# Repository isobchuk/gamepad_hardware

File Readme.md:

# Schematic and PCB fo simple custom retro gamepad

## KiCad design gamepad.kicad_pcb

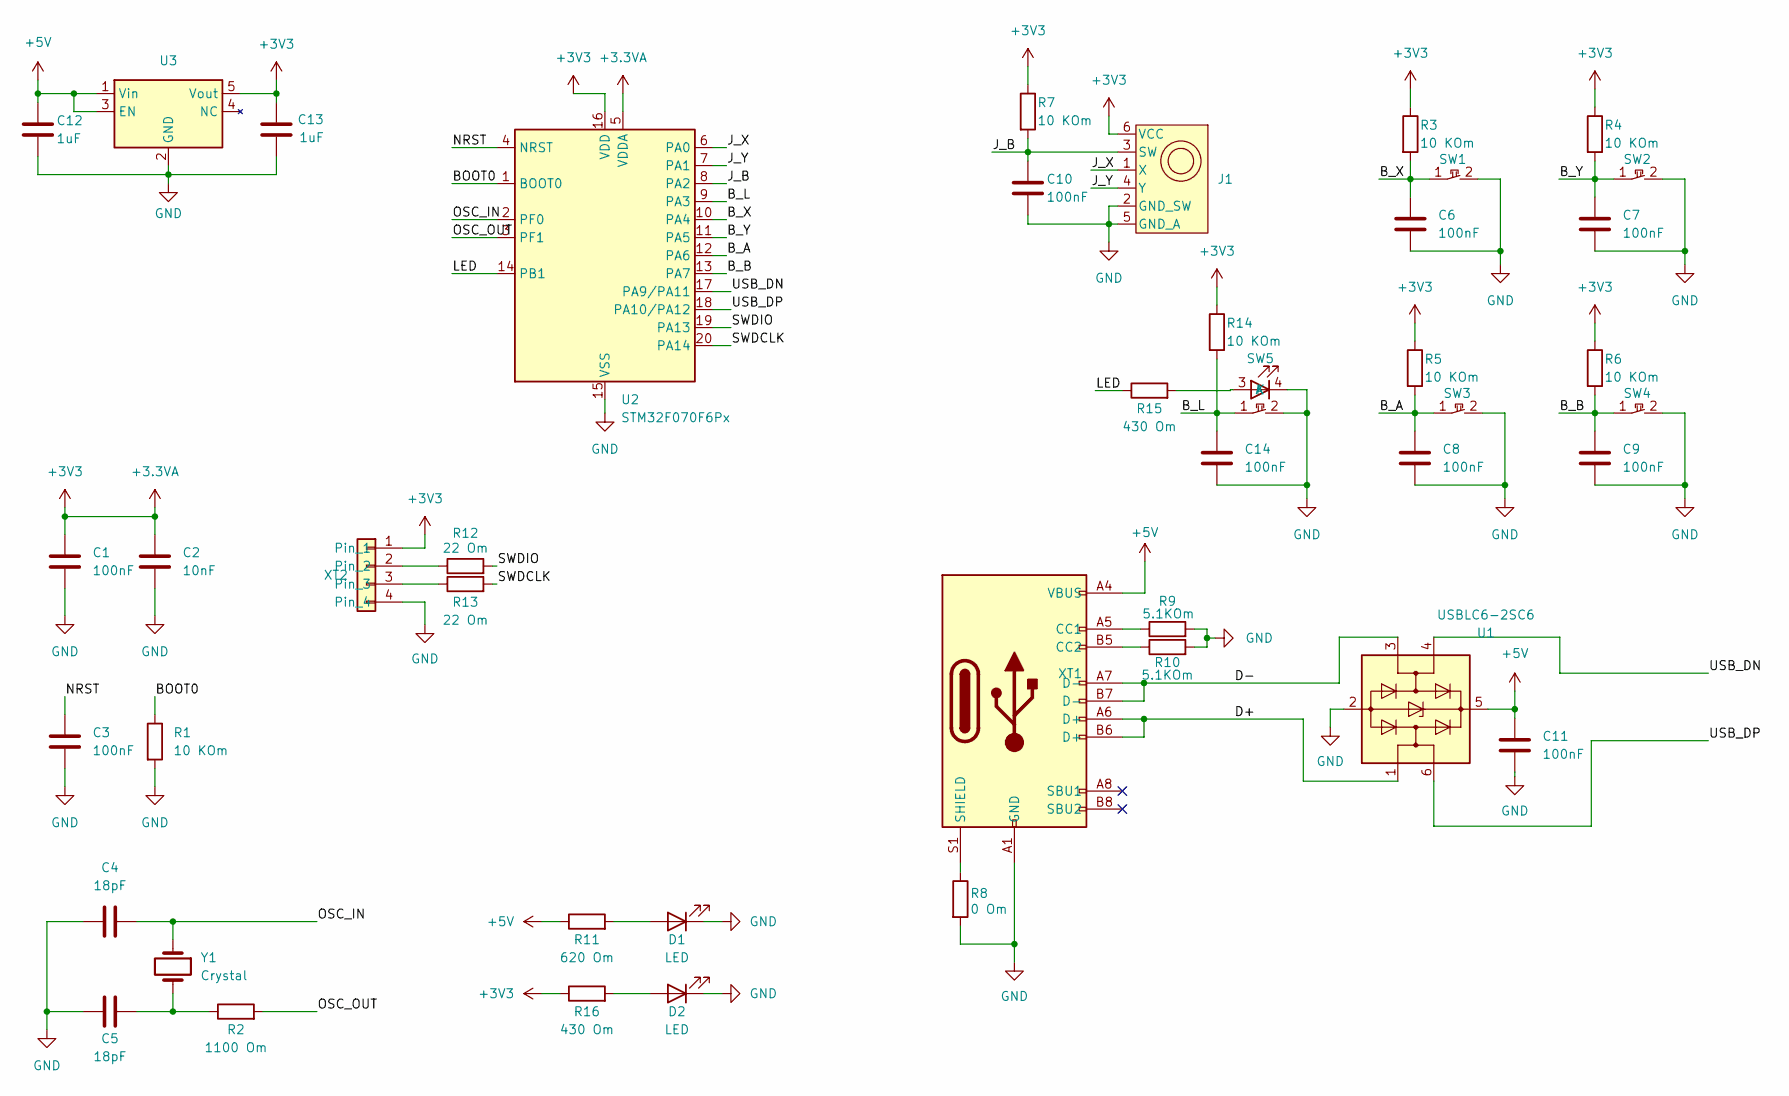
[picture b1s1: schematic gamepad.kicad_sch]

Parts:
C1, C3, C6, C7, C8, C9, C10, C11, C14: 100nF; C_0603_1608Metric
C2: 10nF; C_0603_1608Metric
C4, C5: 18pF; C_0603_1608Metric
C12, C13: 1uF; C_0603_1608Metric
D1, D2: LED; LED_0805_2012Metric
J1: Joystick
R1, R3, R4, R5, R6, R7, R14: 10 KOm; R_0603_1608Metric
R2: 1100 Om; R_0603_1608Metric
R8: 0 Om; R_0603_1608Metric
R9, R10: 5.1KOm; R_0603_1608Metric
R11: 620 Om; R_0603_1608Metric
R12, R13: 22 Om; R_0603_1608Metric
R15, R16: 430 Om; R_0603_1608Metric
SW1, SW2, SW3, SW4: Button_12mm
SW5: Button_12mm_LED
U1: USBLC6-2SC6; SOT-23-6
U2: STM32F070F6Px; TSSOP-20_4.4x6.5mm_P0.65mm
U3: SOT-23-5
XT1: USB_C_2.0_16P
XT2: JST_EH_B4B-EH-A_1x04_P2.50mm_Vertical
Y1: Crystal; Crystal_SMD_5032-2Pin_5.0x3.2mm

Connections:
+3.3VA: C1.1, C2.1, C13.1, J1.6 (VCC), R3.1, R4.1, R5.1, R6.1, R7.1, R14.1, R16.1, U2.5 (VDDA), U2.16 (VDD), U3.5 (Vout), XT2.1; also elsewhere on the board
+5V: C11.1, C12.1, R11.1, U1.5 (VBUS), U3.1 (Vin), U3.3 (EN), XT1.A4 (VBUS), XT1.A9 (VBUS), XT1.B4 (VBUS), XT1.B9 (VBUS); also elsewhere on the board
/BOOT0: R1.1, U2.1 (BOOT0)
/B_A: C8.1, R5.2, SW3.1, U2.12 (PA6)
/B_B: C9.1, R6.2, SW4.1, U2.13 (PA7)
/B_L: C14.1, R14.2, SW5.1, U2.9 (PA3)
/B_X: C6.1, R3.2, SW1.1, U2.10 (PA4)
/B_Y: C7.1, R4.2, SW2.1, U2.11 (PA5)
/D+: U1.1 (I/O1), XT1.A6 (D+), XT1.B6 (D+)
/D-: U1.3 (I/O2), XT1.A7 (D-), XT1.B7 (D-)
/J_B: C10.1, J1.3 (SW), R7.2, U2.8 (PA2)
/J_X: J1.1 (X), U2.6 (PA0)
/J_Y: J1.4 (Y), U2.7 (PA1)
/LED: R15.1, U2.14 (PB1)
/NRST: C3.1, U2.4 (NRST)
/OSC_IN: C4.2, U2.2 (PF0), Y1.1
/OSC_OUT: R2.2, U2.3 (PF1)
/SWDCLK: R13.2, U2.20 (PA14)
/SWDIO: R12.2, U2.19 (PA13)
/USB_DN: U1.4 (I/O2), U2.17 (PA9/PA11)
/USB_DP: U1.6 (I/O1), U2.18 (PA10/PA12)
GND: C1.2, C2.2, C3.2, C4.1, C5.1, C6.2, C7.2, C8.2, C9.2, C10.2, C11.2, C12.2, C13.2, C14.2, D1.1 (K), D2.1 (K), J1.2 (GND_SW), J1.5 (GND_A), R1.2, R8.2, R9.2, R10.2, SW1.2, SW2.2, SW3.2, SW4.2, SW5.2, SW5.4 (K), U1.2 (GND), U2.15 (VSS), U3.2 (GND), XT1.A1 (GND), XT1.A12 (GND), XT1.B1 (GND), XT1.B12 (GND), XT2.4; also elsewhere on the board
unnamed: C5.2, R2.1, Y1.2
unnamed: D1.2 (A), R11.2
unnamed: D2.2 (A), R16.2
unnamed: R15.2, SW5.3 (A)
unnamed: R9.1, XT1.A5 (CC1)
unnamed: R10.1, XT1.B5 (CC2)
unnamed: R8.1, XT1.S1 (SHIELD)
unnamed: R12.1, XT2.2
unnamed: R13.1, XT2.3

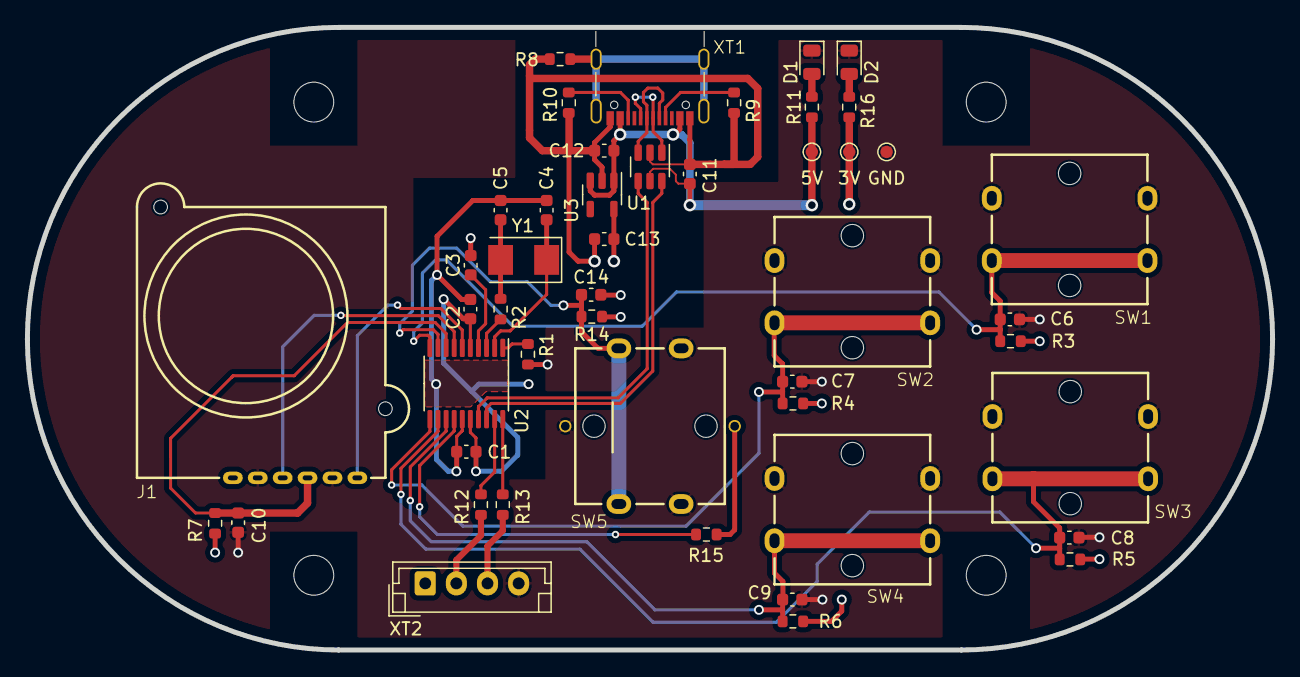
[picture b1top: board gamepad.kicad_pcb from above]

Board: 4 copper layers, 100.0 x 50.0 mm, 47 parts (0 on the bottom side), 31 nets.

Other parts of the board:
3V, 5V: TestPoint_Pad_D1.0mm
GND: TestPoint_Pad_D1.0mm

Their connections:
+3.3VA: 3V.1; also elsewhere on the board
+5V: 5V.1; also elsewhere on the board
GND: GND.1; also elsewhere on the board

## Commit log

2023-11-25 Create LICENSE
